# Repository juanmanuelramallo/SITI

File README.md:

# SITI
Sistema Integral de Transporte Inteligente - Trabajo final para Taller de Proyecto I - UNLP

## Documentación
Se encuentran todos los archivos requeridos durante el desarrollo del proyecto. Ya sean hojas de datos, gráficos, material adicional entre otras cosas.

## Hardware
_Recopilando información_

##Software
Se encuentra el versión final del proyecto, para ser compilada y descargada en un módulo SITI usando la EDU-CIAA-NXP.

En el archivo `INFORME SITI FINAL.pdf` se puede observar a detalle la implementación del sistema.

Integrantes del proyecto:
- Cobanera Santiago
- Iglesias Ramiro
- Pontetto Axel
- Ramallo Juan Manuel

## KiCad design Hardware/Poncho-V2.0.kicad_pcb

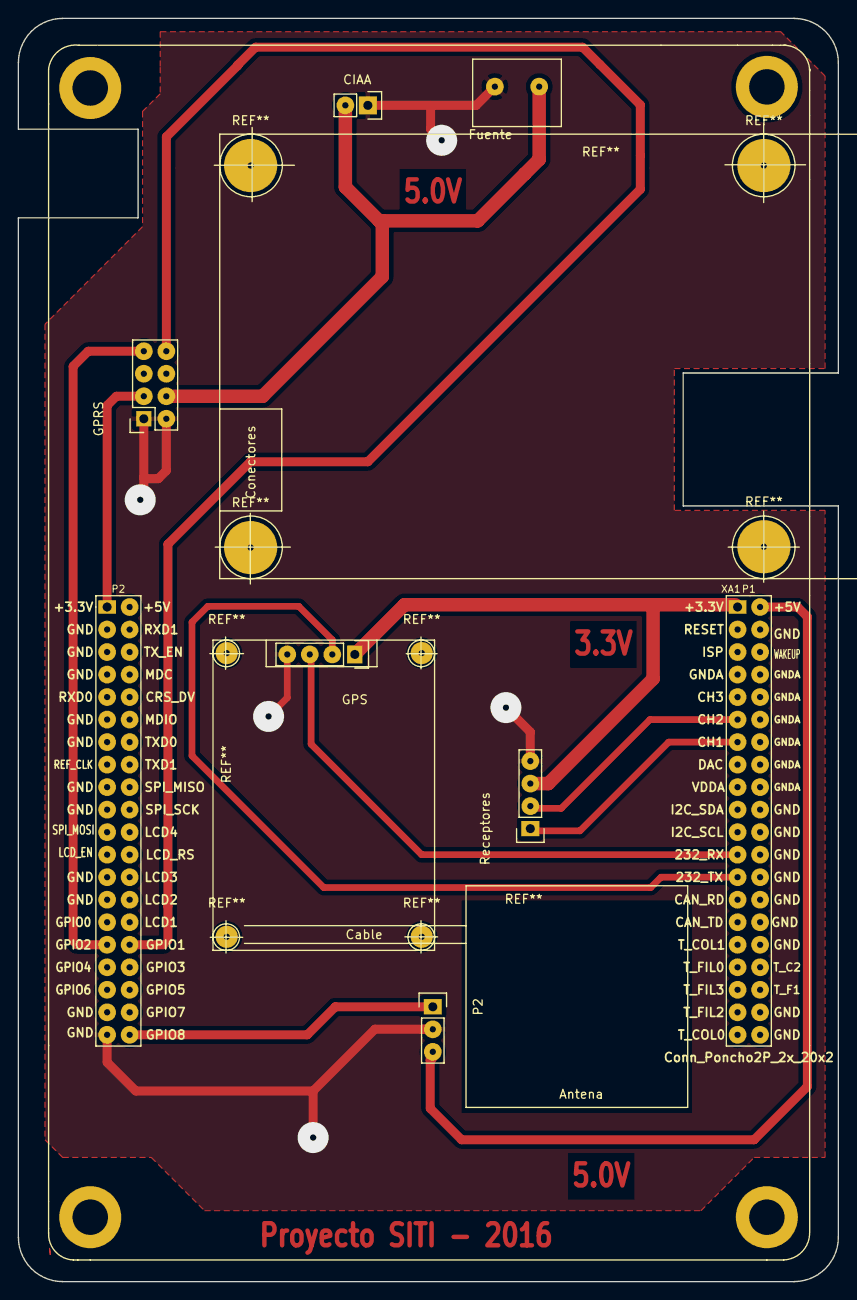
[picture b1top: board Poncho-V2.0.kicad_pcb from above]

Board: 2 copper layers, 92.5 x 142.5 mm, 7 parts (0 on the bottom side), 12 nets.

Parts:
CIAA: AlimentacionCIAA; Socket_Strip_Straight_1x02
Fuente: Fuente
GPRS: GPRS; Socket_Strip_Straight_2x04
GPS: GPS; Socket_Strip_Straight_1x04
P2: Emisores; Socket_Strip_Straight_1x03
Receptores: Receptores; Socket_Strip_Straight_1x04
XA1: Conn_Poncho2P_2x_20x2; poncho_grande

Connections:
3.3V: GPRS.3, XA1.41
5V: P2.3, XA1.2
+3.3V: GPS.1, Receptores.3, XA1.1
ADC_CH1: Receptores.1, XA1.13
ADC_CH2: Receptores.2, XA1.11
GND: CIAA.1, Fuente.2, GPRS.1, GPRS.2, GPS.4, P2.2, Receptores.4, XA1.4, XA1.79
GPIO1: GPRS.8, XA1.72
GPIO2: GPRS.7, XA1.71
GPIO8: P2.1, XA1.80
unnamed: CIAA.2, Fuente.1, GPRS.4
RX232: GPS.3, XA1.23
TX232: GPS.2, XA1.25

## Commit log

2017-02-20 Initial commit, all documentation, all software
2017-02-20 Set theme jekyll-theme-minimal
2017-02-20 Set theme jekyll-theme-slate
2017-02-21 New version of informe
2017-02-21 Like rolling back
2017-02-21 Removing old informe
2017-02-22 Hardware files added, software folder updated
2017-02-23 More time to execute gprs mef
2017-02-24 Contador de pasajeros fixed, corrección de punto medio
2017-02-24 For contador to have a better console displaying
